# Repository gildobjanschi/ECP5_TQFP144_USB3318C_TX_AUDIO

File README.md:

# ECP5 High Speed USB Audio Board
This project aims to implement a High Speed USB audio interface using the Lattice Semiconductor ECP5 FPGA coupled with a USB3318C ULPI USB interface.

## Software
The FPGA Verilog software for the board is currently being developed in a private Github project. Once the board and the code are verified this page will be updated with a link to that project.

## Project Status
The board was manufactured and it is fully functional.

[Schematic PDF](https://github.com/gildobjanschi/ECP5_TQFP144_USB3318C_TX_AUDIO/blob/main/kicad/ECP5%20Audio%20Tx.pdf)

## How to setup KiCAD
Checkout the project and open it. In the Configure Paths dialog add: Name: ECP5_AUDIO and Path: "full path to your GitHub directory"/GitHub/ECP5_TQFP144_USB3318C_TX_AUDIO

In the Manage Symbol Libraries click the Project Specific Libraries and add: Name: ECP5_AUDIO and Library Path: ${ECP5_AUDIO}/symbols/Symbols.kicad_sym

In the Manage Footprint Libraries click the Project Specific Libraries and add: Name: ECP5_AUDIO and Library Path: ${ECP5_AUDIO}/footprints/Footprints.pretty

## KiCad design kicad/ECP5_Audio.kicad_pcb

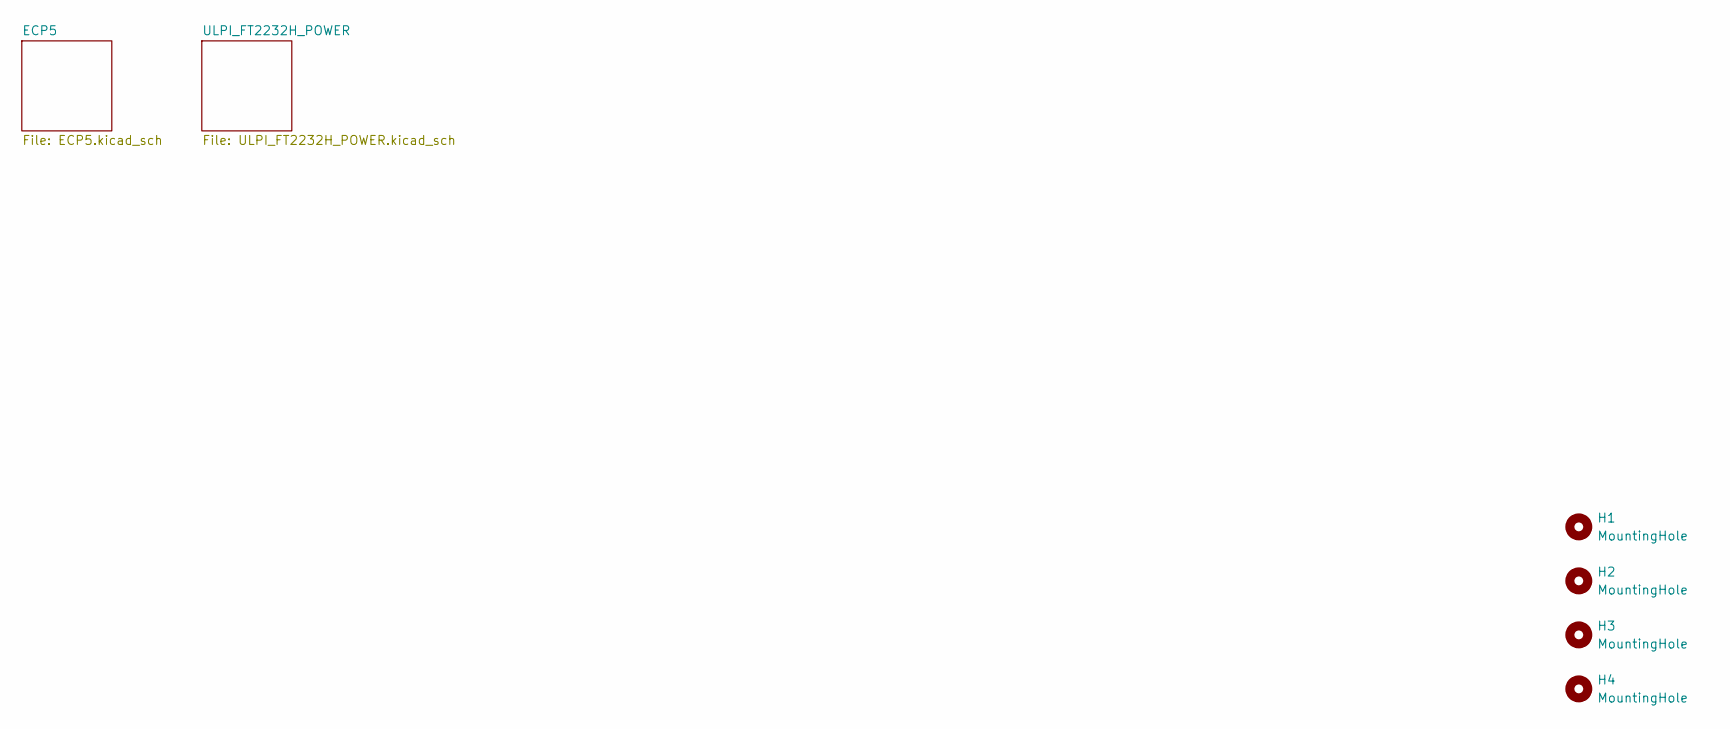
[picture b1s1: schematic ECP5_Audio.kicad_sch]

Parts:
H1, H2, H3, H4: MountingHole; MountingHole_3.2mm_M3

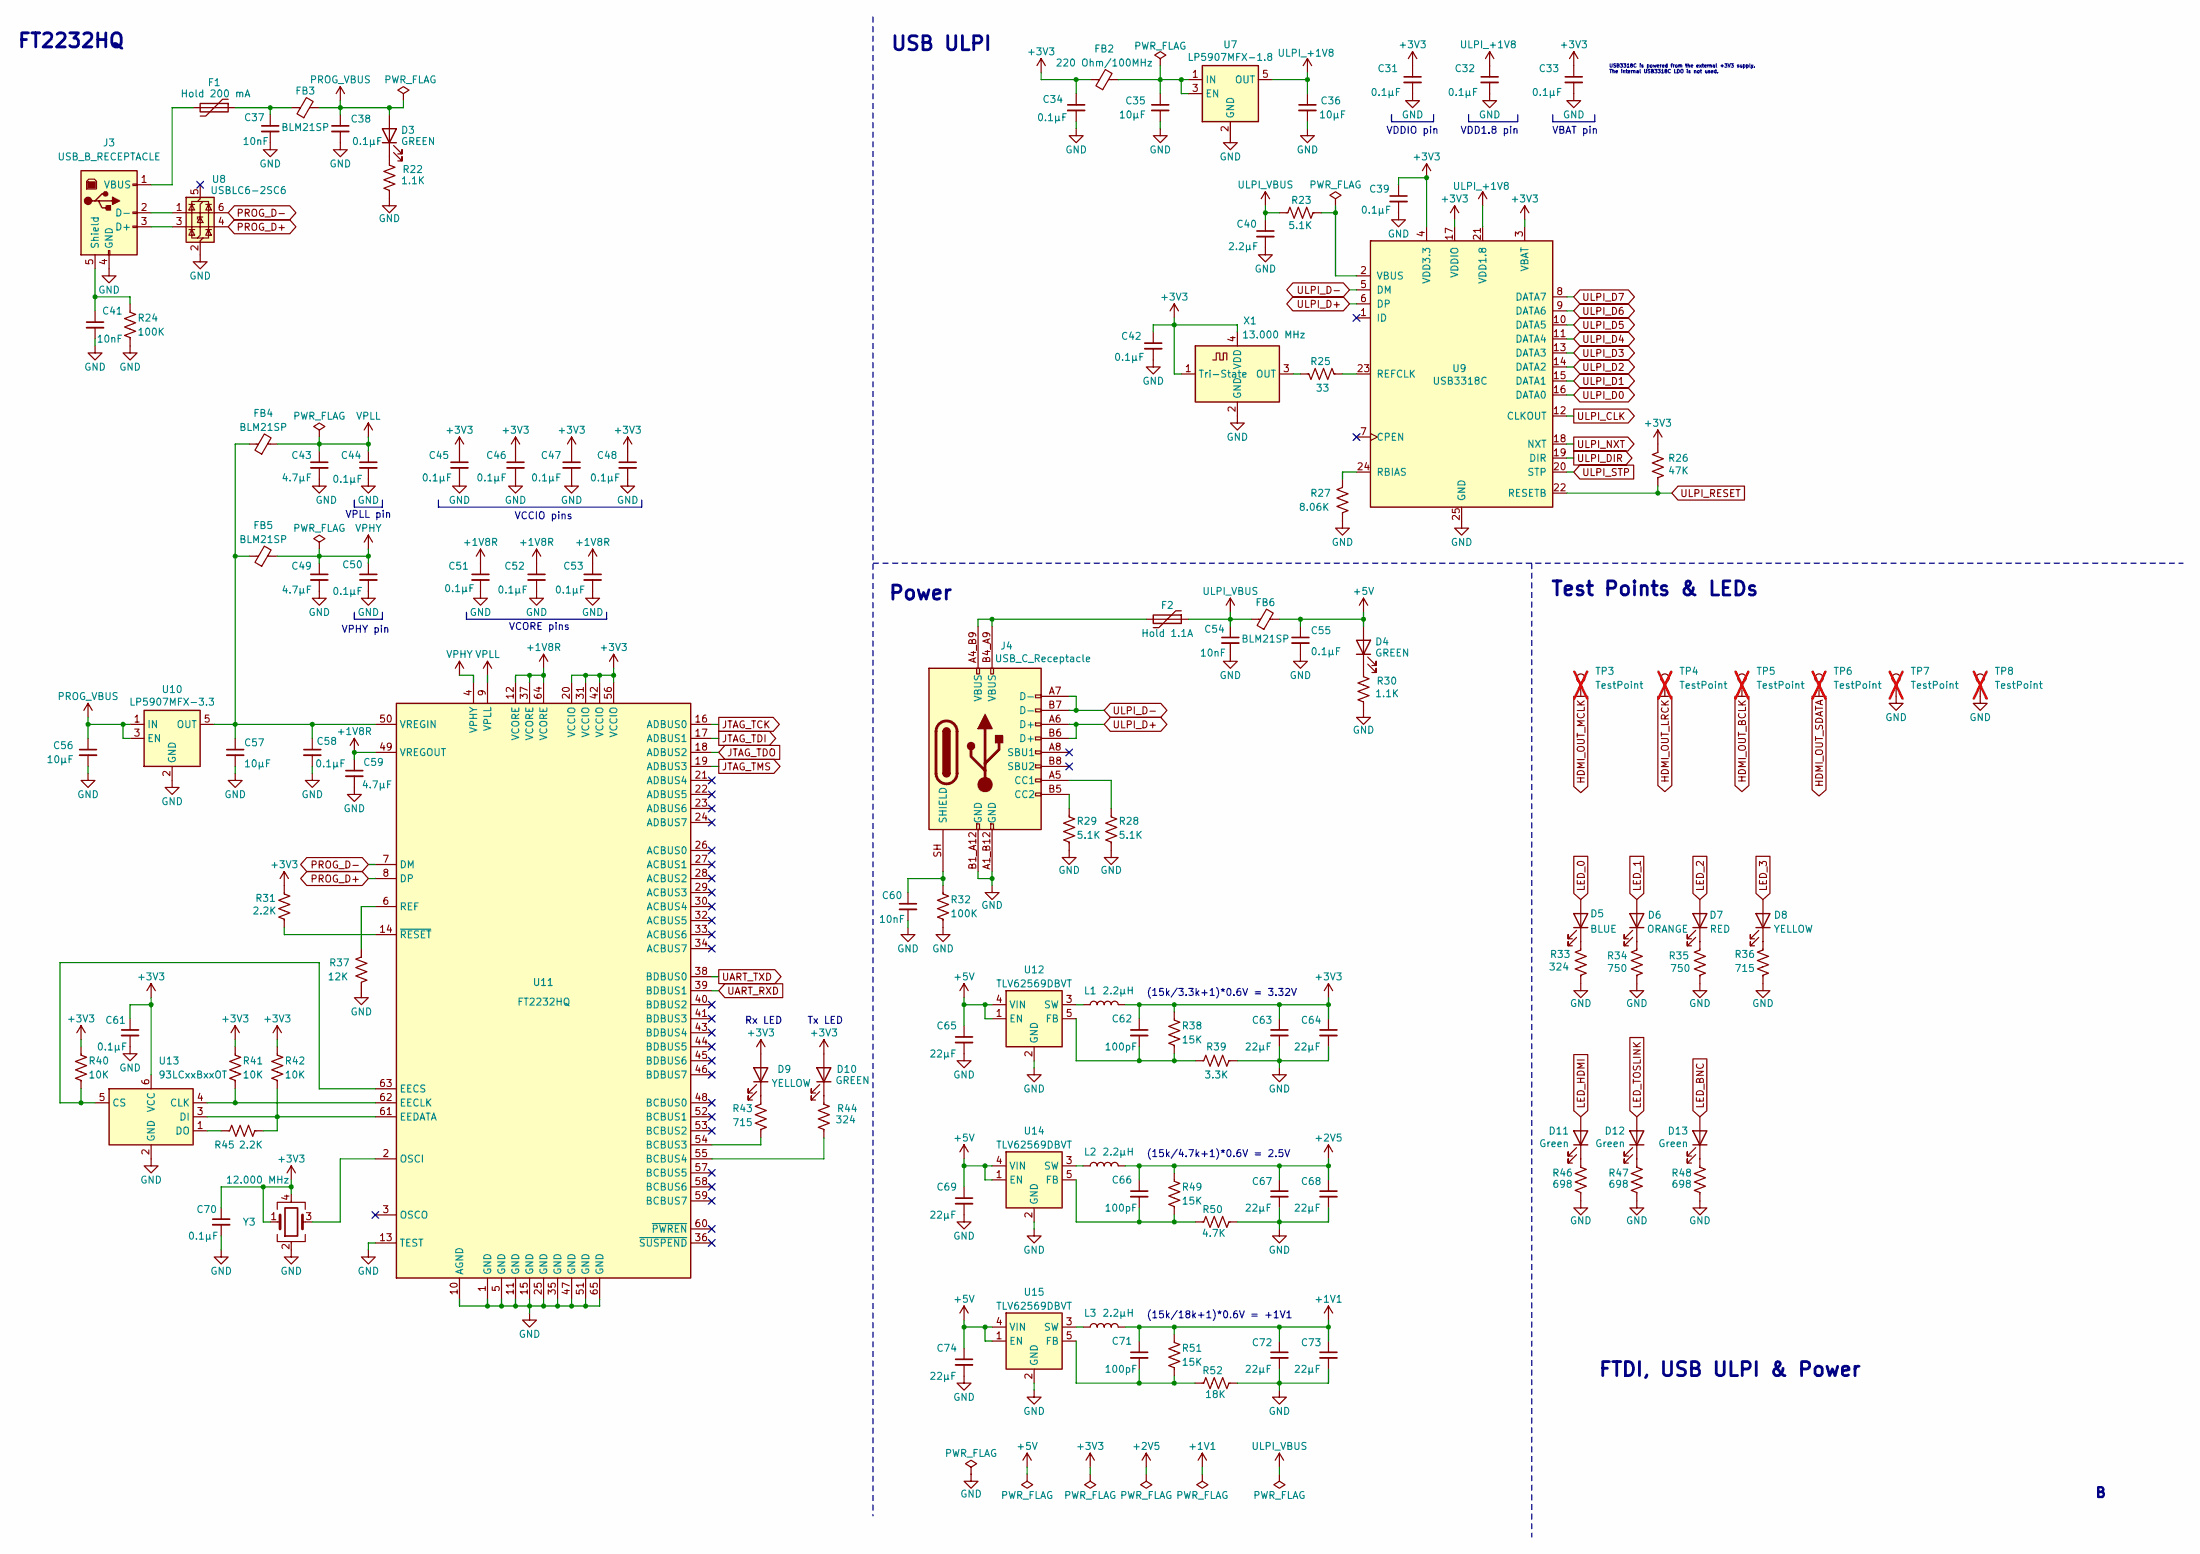
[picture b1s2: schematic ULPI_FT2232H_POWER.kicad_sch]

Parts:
C31, C32, C33, C34, C38, C39, C42, C44, C45, C46, C47, C48, C50, C51, C52, C53, C55, C58, C61, C70: 0.1µF; C_0603_1608Metric; MPN CL10B104KB8NNNC
C35, C36, C56, C57: 10µF; C_0805_2012Metric; MPN CL21B106KOQNNNE
C37, C41, C54, C60: 10nF; C_0603_1608Metric; MPN CL10B103KB8NNNC
C40: 2.2µF; C_0603_1608Metric; MPN CL10B225KP8NNNC
C43, C49, C59: 4.7µF; C_0603_1608Metric; MPN CL10A475KL8NRNC
C62, C66, C71: 100pF; C_0603_1608Metric; MPN CL10C101FB81PNC
C63, C64, C65, C67, C68, C69, C72, C73, C74: 22µF; C_0805_2012Metric; MPN CL21A226KOQNNNE
D3, D4, D10: GREEN; LED_0603_1608Metric; MPN APT1608LZGCK
D5: BLUE; LED_0603_1608Metric; MPN APT1608LVBC/D
D6: ORANGE; LED_0603_1608Metric; MPN APT1608LSECK/J4-PRV
D7: RED; LED_0603_1608Metric; MPN APT1608LSECK/J3-PRV
D8, D9: YELLOW; LED_0603_1608Metric; MPN APT1608LSYCK
D11, D12, D13: Green; Dialight_551-0307F; MPN 5511307F
F1: Hold 200 mA; Bel_Fuse_1812; MPN 0ZCG0020AF2C
F2: Hold 1.1A; Bel_Fuse_1812; MPN 0ZCG0110AF2C
FB2: 220 Ohm/100MHz; L_0603_1608Metric; MPN MPZ1608S221ATA00
FB3, FB4, FB5, FB6: BLM21SP; L_0805_2012Metric; MPN BLM21SP601SN1D
J3: USB_B_RECEPTACLE; CUI_UJ2-BH-BL1-TH; MPN UJ2-BH-BL1-TH
J4: USB_C_Receptacle; GCT_USB4105GFA120; MPN USB4105-GF-A-120
L1, L2, L3: 2.2µH; L_1210_3225Metric; MPN DFE322512F-2R2M=P2
R22, R30: 1.1K; R_0603_1608Metric; MPN ERJ-3EKF1101V
R23, R28, R29: 5.1K; R_0603_1608Metric; MPN ERJ-3EKF5101V
R24, R32: 100K; R_0603_1608Metric; MPN ERJ-3EKF1003V
R25: 33; R_0603_1608Metric; MPN ERJ-3EKF33R0V
R26: 47K; R_0603_1608Metric; MPN ERJ-3EKF4702V
R27: 8.06K; R_0603_1608Metric; MPN ERJ-3EKF8061V
R31, R45: 2.2K; R_0603_1608Metric; MPN ERJ-3EKF2201V
R33, R44: 324; R_0603_1608Metric; MPN ERJ-3EKF3240V
R34, R35: 750; R_0603_1608Metric; MPN ERJ-3EKF7500V
R36, R43: 715; R_0603_1608Metric; MPN ERJ-3EKF7150V
R37: 12K; R_0603_1608Metric; MPN ERJ-3EKF1202V
R38, R49, R51: 15K; R_0603_1608Metric; MPN ERJ-3EKF1502V
R39: 3.3K; R_0603_1608Metric; MPN ERJ-3EKF3301V
R40, R41, R42: 10K; R_0603_1608Metric; MPN ERJ-3EKF1002V
R46, R47, R48: 698; R_0603_1608Metric; MPN ERJ-3EKF6980V
R50: 4.7K; R_0603_1608Metric; MPN ERJ-3EKF4701V
R52: 18K; R_0603_1608Metric; MPN ERJ-3EKF1802V
TP3, TP4, TP5, TP6: TestPoint; TestPoint_Keystone_5000-5004_Miniature; MPN 5004; not fitted
TP7, TP8: TestPoint; TestPoint_Keystone_5000-5004_Miniature; MPN 5001; not fitted
U7: LP5907MFX-1.8; SOT-23-5; MPN LP5907MFX-1.8/NOPB
U8: USBLC6-2SC6; SOT-23-6; MPN USBLC6-2SC6
U9: USB3318C; QFN-24-1EP_4x4mm_P0.5mm_EP2.65x2.65mm_ThermalVias; MPN USB3318C-CP-TR
U10: LP5907MFX-3.3; SOT-23-5; MPN LP5907MFX-3.3/NOPB
U11: FT2232HQ; QFN-64-1EP_9x9mm_P0.5mm_EP4.35x4.35mm; MPN FT2232HQ-REEL
U12, U14, U15: TLV62569DBVT; SOT-23-5; MPN TLV62569DBVT
U13: 93LCxxBxxOT; SOT-23-6; MPN 93LC56BT-I/OT
X1: 13.000 MHz; Oscillator_SMD_ECS_2520MV-xxx-xx-4Pin_2.5x2.0mm; MPN ECS-2520MV-130-BN-TR
Y3: 12.000 MHz; Oscillator_SMD_ECS_2520MV-xxx-xx-4Pin_2.5x2.0mm; MPN SG-210STF 12.0000ML3

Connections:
+1V1: C71.1, C72.1, C73.1, L3.2, R51.1; also elsewhere on the board
+1V8R: C51.1, C52.1, C53.1, C59.1, U11.12 (VCORE), U11.37 (VCORE), U11.49 (VREGOUT), U11.64 (VCORE)
+2V5: C66.1, C67.1, C68.1, L2.2, R49.1; also elsewhere on the board
+3V3: C31.1, C33.1, C34.1, C39.1, C42.1, C45.1, C46.1, C47.1, C48.1, C61.1, C62.1, C63.1, C64.1, C70.1, D9.2 (A), D10.2 (A), FB2.1, L1.2, R26.2, R31.1, R38.1, R40.1, R41.1, R42.1, U9.3 (VBAT), U9.4 (VDD3.3), U9.17 (VDDIO), U11.20 (VCCIO), U11.31 (VCCIO), U11.42 (VCCIO), U11.56 (VCCIO), U13.6 (VCC), X1.1 (Tri-State), X1.4 (VDD), Y3.1, Y3.4; also elsewhere on the board
+5V: C55.1, C65.1, C69.1, C74.1, D4.2 (A), FB6.2, U12.1 (EN), U12.4 (VIN), U14.1 (EN), U14.4 (VIN), U15.1 (EN), U15.4 (VIN); also elsewhere on the board
GND: C31.2, C32.2, C33.2, C34.2, C35.2, C36.2, C37.2, C38.2, C39.2, C40.2, C41.2, C42.2, C43.2, C44.2, C45.2, C46.2, C47.2, C48.2, C49.2, C50.2, C51.2, C52.2, C53.2, C54.2, C55.2, C56.2, C57.2, C58.2, C59.2, C60.2, C61.2, C63.2, C64.2, C65.2, C67.2, C68.2, C69.2, C70.2, C72.2, C73.2, C74.2, J3.4 (GND), J4.A1_B12 (GND), J4.B1_A12 (GND), R22.2, R24.2, R27.2, R28.2, R29.2, R30.2, R32.2, R33.2, R34.2, R35.2, R36.2, R37.2, R39.2, R46.2, R47.2, R48.2, R50.2, R52.2, TP7.1, TP8.1, U7.2 (GND), U8.2 (GND), U9.25 (GND), U10.2 (GND), U11.1 (GND), U11.5 (GND), U11.10 (AGND), U11.11 (GND), U11.13 (TEST), U11.15 (GND), U11.25 (GND), U11.35 (GND), U11.47 (GND), U11.51 (GND), U11.65 (GND), U12.2 (GND), U13.2 (GND), U14.2 (GND), U15.2 (GND), X1.2 (GND), Y3.2; also elsewhere on the board
HDMI_OUT_BCLK: TP5.1; also elsewhere on the board
HDMI_OUT_LRCK: TP4.1; also elsewhere on the board
HDMI_OUT_MCLK: TP3.1; also elsewhere on the board
HDMI_OUT_SDATA: TP6.1; also elsewhere on the board
JTAG_TCK: U11.16 (ADBUS0); also elsewhere on the board
JTAG_TDI: U11.17 (ADBUS1); also elsewhere on the board
JTAG_TDO: U11.18 (ADBUS2); also elsewhere on the board
JTAG_TMS: U11.19 (ADBUS3); also elsewhere on the board
LED_0: D5.2 (A); also elsewhere on the board
LED_1: D6.2 (A); also elsewhere on the board
LED_2: D7.2 (A); also elsewhere on the board
LED_3: D8.2 (A); also elsewhere on the board
LED_BNC: D13.2 (A); also elsewhere on the board
LED_HDMI: D11.2 (A); also elsewhere on the board
LED_TOSLINK: D12.2 (A); also elsewhere on the board
unnamed: C37.1, F1.1, FB3.1
unnamed: D3.1 (K), R22.1
unnamed: D4.1 (K), R30.1
unnamed: D5.1 (K), R33.1
unnamed: D6.1 (K), R34.1
unnamed: D7.1 (K), R35.1
unnamed: D8.1 (K), R36.1
unnamed: D9.1 (K), R43.1
unnamed: D10.1 (K), R44.1
unnamed: D11.1 (K), R46.1
unnamed: D12.1 (K), R47.1
unnamed: D13.1 (K), R48.1
unnamed: F2.2, J4.A4_B9 (VBUS), J4.B4_A9 (VBUS)
unnamed: J3.3 (D+), U8.3 (I/O2)
unnamed: J3.2 (D-), U8.1 (I/O1)
unnamed: C41.1, J3.5 (Shield), R24.1
unnamed: F1.2, J3.1 (VBUS)
unnamed: J4.A5 (CC1), R28.1
unnamed: J4.B5 (CC2), R29.1
unnamed: C60.1, J4.SH (SHIELD), R32.1
unnamed: C35.1, FB2.2, U7.1 (IN), U7.3 (EN)
unnamed: R27.1, U9.24 (RBIAS)
unnamed: R25.2, U9.23 (REFCLK)
unnamed: R23.1, U9.2 (VBUS)
unnamed: C57.1, C58.1, FB4.1, FB5.1, U10.5 (OUT), U11.50 (VREGIN)
unnamed: R43.2, U11.54 (BCBUS3)
unnamed: R44.2, U11.55 (BCBUS4)
unnamed: R41.2, U11.62 (EECLK), U13.4 (CLK)
unnamed: R40.2, U11.63 (EECS), U13.5 (CS)
unnamed: R42.2, R45.2, U11.61 (EEDATA), U13.3 (DI)
unnamed: U11.2 (OSCI), Y3.3
unnamed: R37.1, U11.6 (REF)
unnamed: R31.2, U11.14 (~RESET)
unnamed: C62.2, R38.2, R39.1, U12.5 (FB)
unnamed: L1.1, U12.3 (SW)
unnamed: R45.1, U13.1 (DO)
unnamed: C66.2, R49.2, R50.1, U14.5 (FB)
unnamed: L2.1, U14.3 (SW)
unnamed: C71.2, R51.2, R52.1, U15.5 (FB)
unnamed: L3.1, U15.3 (SW)
unnamed: R25.1, X1.3 (OUT)
PROG_D+: U8.4 (I/O2), U11.8 (DP)
PROG_D-: U8.6 (I/O1), U11.7 (DM)
PROG_VBUS: C38.1, C56.1, D3.2 (A), FB3.2, U10.1 (IN), U10.3 (EN)
UART_RXD: U11.39 (BDBUS1); also elsewhere on the board
UART_TXD: U11.38 (BDBUS0); also elsewhere on the board
ULPI_+1V8: C32.1, C36.1, U7.5 (OUT), U9.21 (VDD1.8)
ULPI_CLK: U9.12 (CLKOUT); also elsewhere on the board
ULPI_D0: U9.16 (DATA0); also elsewhere on the board
ULPI_D1: U9.15 (DATA1); also elsewhere on the board
ULPI_D2: U9.14 (DATA2); also elsewhere on the board
ULPI_D3: U9.13 (DATA3); also elsewhere on the board
ULPI_D4: U9.11 (DATA4); also elsewhere on the board
ULPI_D5: U9.10 (DATA5); also elsewhere on the board
ULPI_D6: U9.9 (DATA6); also elsewhere on the board
ULPI_D7: U9.8 (DATA7); also elsewhere on the board
ULPI_D+: J4.A6 (D+), J4.B6 (D+), U9.6 (DP)
ULPI_D-: J4.A7 (D-), J4.B7 (D-), U9.5 (DM)
ULPI_DIR: U9.19 (DIR); also elsewhere on the board
ULPI_NXT: U9.18 (NXT); also elsewhere on the board
ULPI_RESET: R26.1, U9.22 (RESETB); also elsewhere on the board
ULPI_STP: U9.20 (STP); also elsewhere on the board
ULPI_VBUS: C40.1, C54.1, F2.1, FB6.1, R23.2
VPHY: C49.1, C50.1, FB5.2, U11.4 (VPHY)
VPLL: C43.1, C44.1, FB4.2, U11.9 (VPLL)

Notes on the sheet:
VPLL pin
VCCIO pins
(15k/4.7k+1)*0.6V = 2.5V
Test Points & LEDs
Power
VCORE pins
VPHY pin
(15k/18k+1)*0.6V = +1V1
VDD1.8 pin
USB ULPI
Rx LED
FTDI, USB ULPI & Power
USB3318C is powered from the external +3V3 supply. The internal USB3318C LDO is not used.
Tx LED
VDDIO pin
VBAT pin
FT2232HQ
(15k/3.3k+1)*0.6V = 3.32V

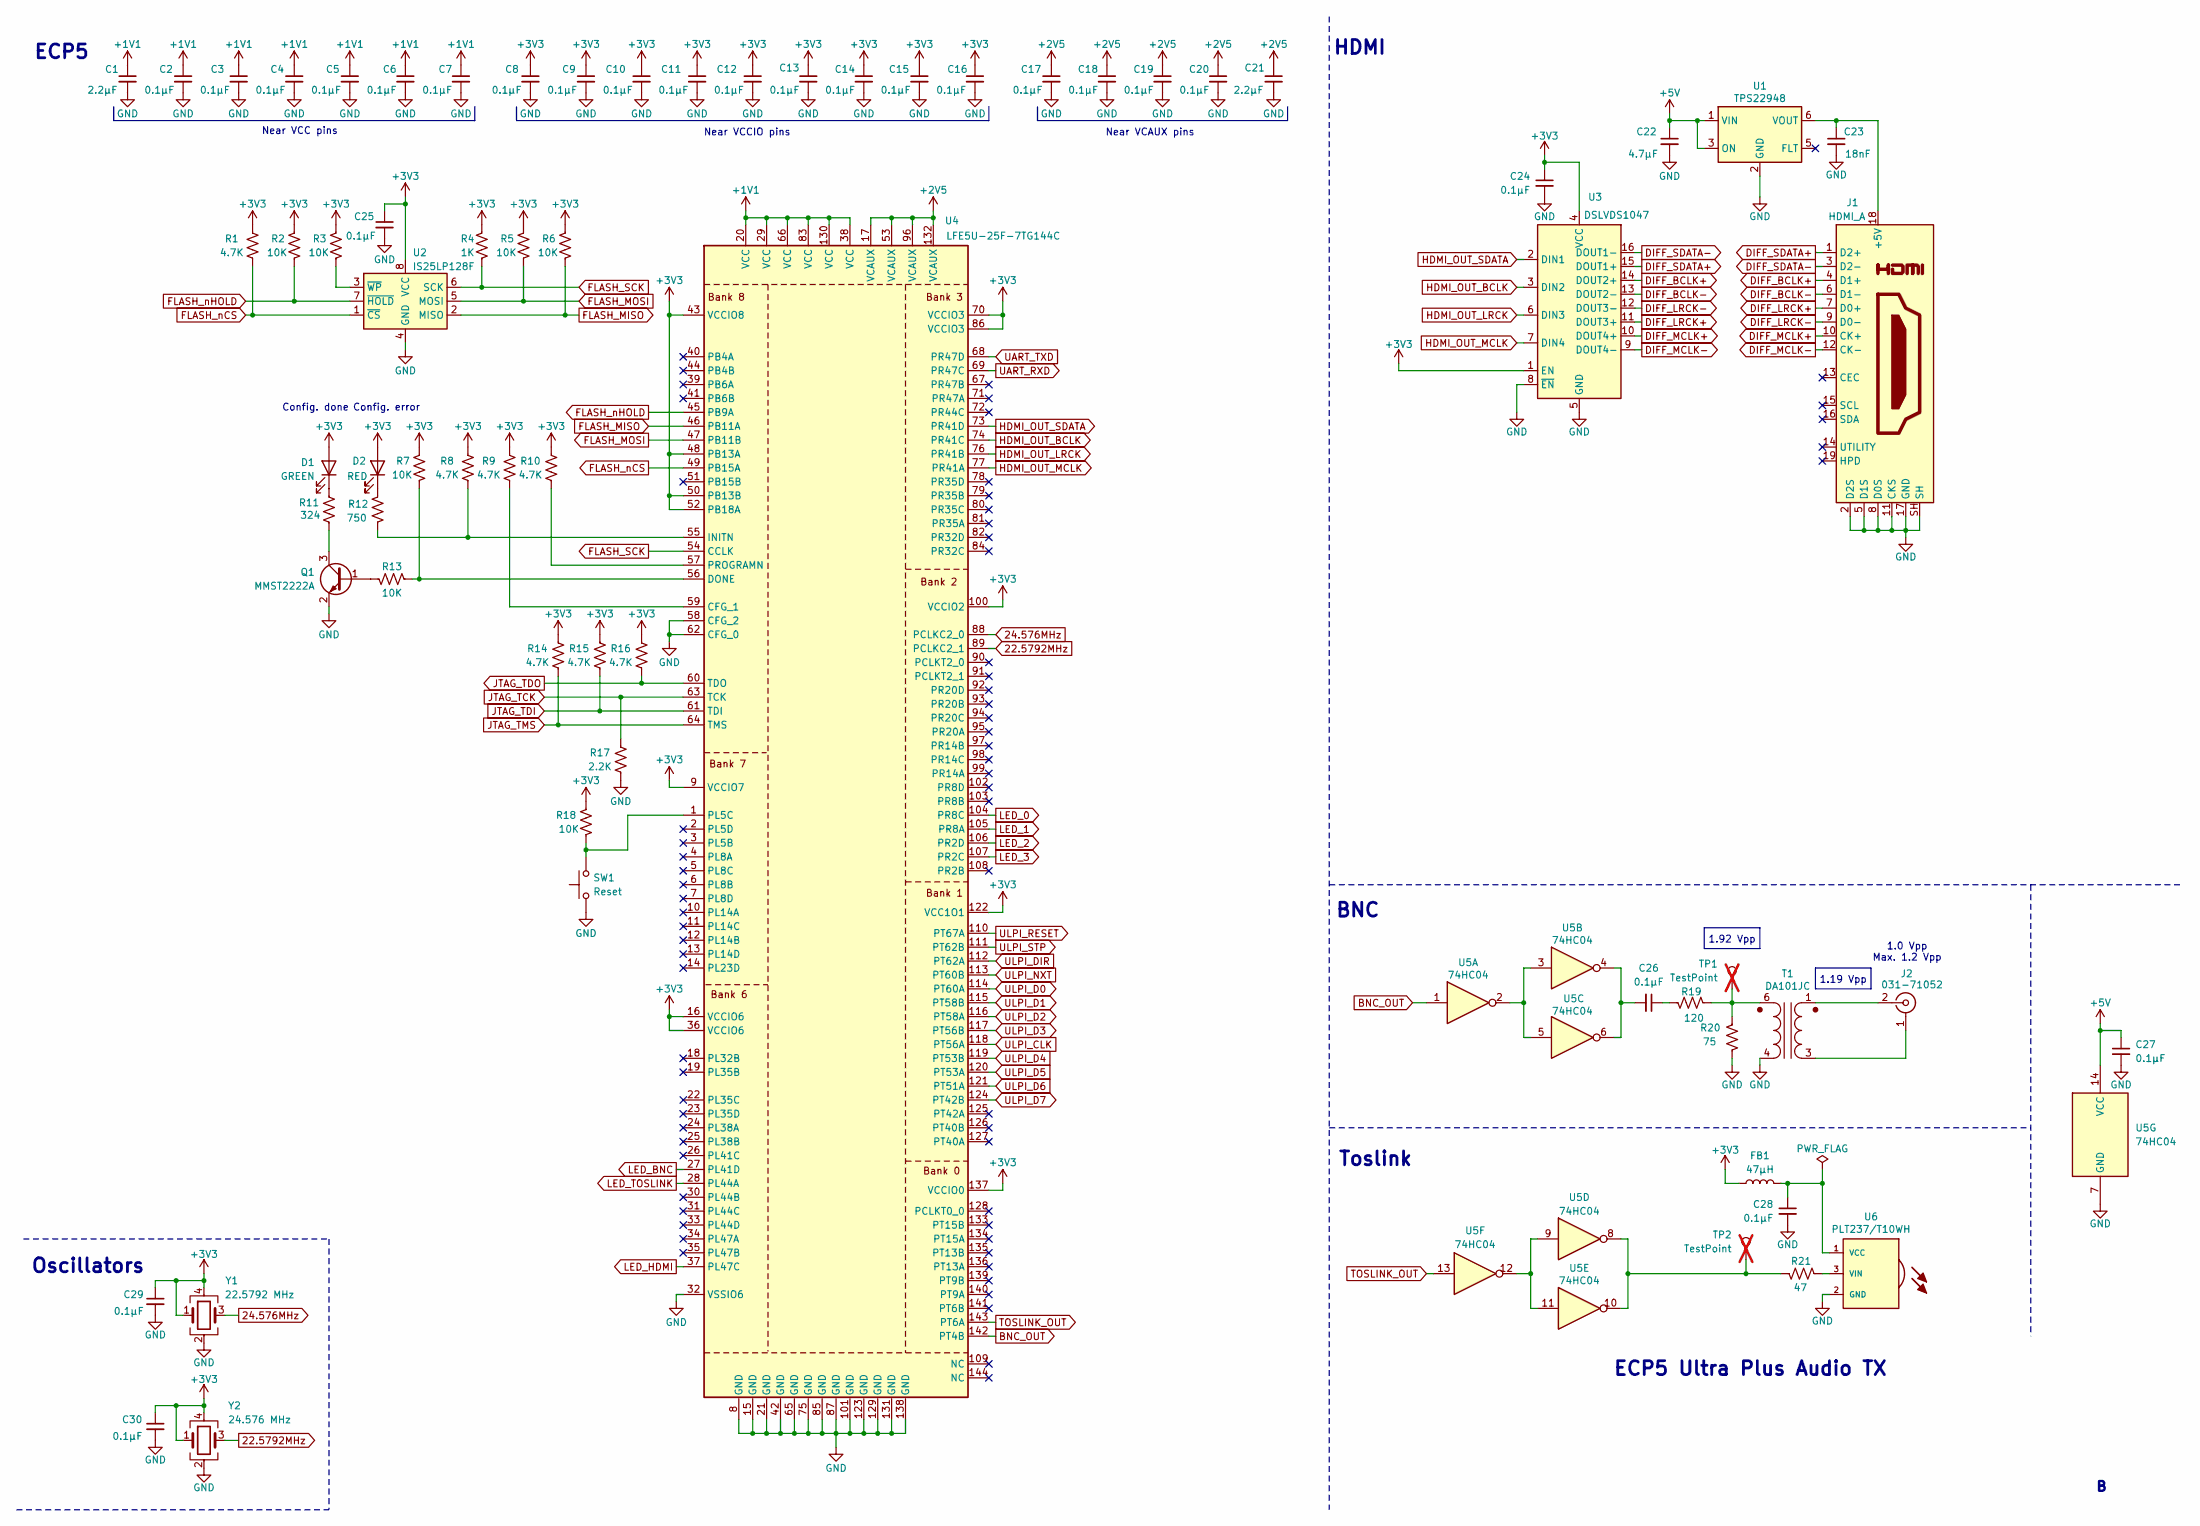
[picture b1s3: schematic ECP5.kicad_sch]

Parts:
C1, C21: 2.2µF; C_0603_1608Metric; MPN CL10B225KP8NNNC
C2, C3, C4, C5, C6, C7, C8, C9, C10, C11, C12, C13, C14, C15, C16, C17, C18, C19, C20, C24, C25, C26, C27, C28, C29, C30: 0.1µF; C_0603_1608Metric; MPN CL10B104KB8NNNC
C22: 4.7µF; C_0603_1608Metric; MPN CL10A475KL8NRNC
C23: 18nF; C_0603_1608Metric; MPN CC0603KRX7R9BB183
D1: GREEN; LED_0603_1608Metric; MPN APT1608LZGCK
D2: RED; LED_0603_1608Metric; MPN APT1608LSECK/J3-PRV
FB1: 47µH; L_0805_2012Metric; MPN LQM21DN470M70L
J1: HDMI_A; AMPHENOL_10029449-001RLF; MPN 10029449-001RLF
J2: 031-71052; BNC_Amphenol_031-71052_Horizontal; MPN 031-71052
Q1: MMST2222A; SOT-323_SC-70; MPN MMST2222A-7-F
R1, R8, R9, R10, R14, R15, R16: 4.7K; R_0603_1608Metric; MPN ERJ-3EKF4701V
R2, R3, R5, R6, R7, R13, R18: 10K; R_0603_1608Metric; MPN ERJ-3EKF1002V
R4: 1K; R_0603_1608Metric; MPN ERJ-3EKF1001V
R11: 324; R_0603_1608Metric; MPN ERJ-3EKF3240V
R12: 750; R_0603_1608Metric; MPN ERJ-3EKF7500V
R17: 2.2K; R_0603_1608Metric; MPN ERJ-3EKF2201V
R19: 120; R_0603_1608Metric; MPN ERJ-3EKF1200V
R20: 75; R_0603_1608Metric; MPN ERJ-3EKF75R0V
R21: 47; R_0603_1608Metric; MPN ERJ-3EKF47R0V
SW1: Reset; SW_SPST_PTS645; MPN PTS645SK43SMTR92 LFS
T1: DA101JC; DA101J_MUR; MPN DA101JC
TP1, TP2: TestPoint; TestPoint_Keystone_5000-5004_Miniature; MPN 5004; not fitted
U1: TPS22948; SOT-363_SC-70-6; MPN TPS22948DCKR
U2: IS25LP128F; WDFN-8-1EP_6x5mm_P1.27mm_EP3.4x4mm; MPN IS25LP128-JKLE
U3: DSLVDS1047; TSSOP-16-1EP_4.4x5mm_P0.65mm; MPN DSLVDS1047PWR
U4: LFE5U-25F-7TG144C; TQFP-144_20x20mm_P0.5mm; MPN LFE5U-25F-7TG144C
U5: 74HC04; TSSOP-14_4.4x5mm_P0.65mm; MPN SN74HC04PWR
U6: PLT237/T10WH; PLR135-T10; MPN PLT237/T10WH
Y1: 22.5792 MHz; CCHD-957; MPN CCHD-957-25-22.5792
Y2: 24.576 MHz; CCHD-957; MPN CCHD-957-25-24.576

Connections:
22.5792MHz: U4.89 (PCLKC2_1), Y2.3 (OUT)
24.576MHz: U4.88 (PCLKC2_0), Y1.3 (OUT)
+1V1: C1.1, C2.1, C3.1, C4.1, C5.1, C6.1, C7.1, U4.20 (VCC), U4.29 (VCC), U4.38 (VCC), U4.66 (VCC), U4.83 (VCC), U4.130 (VCC); also elsewhere on the board
+2V5: C17.1, C18.1, C19.1, C20.1, C21.1, U4.17 (VCAUX), U4.53 (VCAUX), U4.96 (VCAUX), U4.132 (VCAUX); also elsewhere on the board
+3V3: C8.1, C9.1, C10.1, C11.1, C12.1, C13.1, C14.1, C15.1, C16.1, C24.1, C25.1, C29.1, C30.1, D1.2 (A), D2.2 (A), FB1.2, R1.2, R2.2, R3.2, R4.1, R5.2, R6.2, R7.2, R8.2, R9.2, R10.2, R14.2, R15.2, R16.2, R18.2, U2.8 (VCC), U3.1 (EN), U3.4 (VCC), U4.9 (VCCIO7), U4.16 (VCCIO6), U4.36 (VCCIO6), U4.43 (VCCIO8), U4.48 (PB13A), U4.50 (PB13B), U4.52 (PB18A), U4.70 (VCCIO3), U4.86 (VCCIO3), U4.100 (VCCIO2), U4.122 (VCC1O1), U4.137 (VCCIO0), Y1.1 (E/D), Y1.4 (VCC), Y2.1 (E/D), Y2.4 (VCC); also elsewhere on the board
+5V: C22.1, C27.1, U1.1 (VIN), U1.3 (ON), U5.14 (VCC); also elsewhere on the board
BNC_OUT: U4.142 (PT4B), U5.1
DIFF_BCLK+: J1.4 (D1+), U3.14 (DOUT2+)
DIFF_BCLK-: J1.6 (D1-), U3.13 (DOUT2-)
DIFF_LRCK+: J1.7 (D0+), U3.11 (DOUT3+)
DIFF_LRCK-: J1.9 (D0-), U3.12 (DOUT3-)
DIFF_MCLK+: J1.10 (CK+), U3.10 (DOUT4+)
DIFF_MCLK-: J1.12 (CK-), U3.9 (DOUT4-)
DIFF_SDATA+: J1.1 (D2+), U3.15 (DOUT1+)
DIFF_SDATA-: J1.3 (D2-), U3.16 (DOUT1-)
FLASH_MISO: R6.1, U2.2 (MISO), U4.46 (PB11A)
FLASH_MOSI: R5.1, U2.5 (MOSI), U4.47 (PB11B)
FLASH_SCK: R4.2, U2.6 (SCK), U4.54 (CCLK)
FLASH_nCS: R1.1, U2.1 (~CS), U4.49 (PB15A)
FLASH_nHOLD: R2.1, U2.7 (~HOLD), U4.45 (PB9A)
GND: C1.2, C2.2, C3.2, C4.2, C5.2, C6.2, C7.2, C8.2, C9.2, C10.2, C11.2, C12.2, C13.2, C14.2, C15.2, C16.2, C17.2, C18.2, C19.2, C20.2, C21.2, C22.2, C23.2, C24.2, C25.2, C27.2, C28.2, C29.2, C30.2, J1.2 (D2S), J1.5 (D1S), J1.8 (D0S), J1.11 (CKS), J1.17 (GND), J1.SH, Q1.2 (E), R17.1, R20.2, SW1.1, T1.4 (SA), U1.2 (GND), U2.4 (GND), U2.9 (GND), U3.5 (GND), U3.8 (~EN), U4.8 (GND), U4.15 (GND), U4.21 (GND), U4.32 (VSSIO6), U4.42 (GND), U4.58 (CFG_2), U4.62 (CFG_0), U4.65 (GND), U4.75 (GND), U4.85 (GND), U4.87 (GND), U4.101 (GND), U4.123 (GND), U4.129 (GND), U4.131 (GND), U4.138 (GND), U5.7 (GND), U6.2 (GND), Y1.2 (GND), Y2.2 (GND); also elsewhere on the board
HDMI_OUT_BCLK: U3.3 (DIN2), U4.74 (PR41C); also elsewhere on the board
HDMI_OUT_LRCK: U3.6 (DIN3), U4.76 (PR41B); also elsewhere on the board
HDMI_OUT_MCLK: U3.7 (DIN4), U4.77 (PR41A); also elsewhere on the board
HDMI_OUT_SDATA: U3.2 (DIN1), U4.73 (PR41D); also elsewhere on the board
JTAG_TCK: R17.2, U4.63 (TCK); also elsewhere on the board
JTAG_TDI: R15.1, U4.61 (TDI); also elsewhere on the board
JTAG_TDO: R16.1, U4.60 (TDO); also elsewhere on the board
JTAG_TMS: R14.1, U4.64 (TMS); also elsewhere on the board
LED_0: U4.104 (PR8C); also elsewhere on the board
LED_1: U4.105 (PR8A); also elsewhere on the board
LED_2: U4.106 (PR2D); also elsewhere on the board
LED_3: U4.107 (PR2C); also elsewhere on the board
LED_BNC: U4.27 (PL41D); also elsewhere on the board
LED_HDMI: U4.37 (PL47C); also elsewhere on the board
LED_TOSLINK: U4.28 (PL44A); also elsewhere on the board
unnamed: C26.1, R19.2
unnamed: C26.2, U5.4, U5.6
unnamed: D1.1 (K), R11.1
unnamed: D2.1 (K), R12.1
unnamed: C23.1, J1.18 (+5V), U1.6 (VOUT)
unnamed: J2.1 (Ext), T1.3 (AB)
unnamed: J2.2 (In), T1.1 (AA)
unnamed: Q1.1 (B), R13.1
unnamed: Q1.3 (C), R11.2
unnamed: R21.2, TP2.1, U5.8, U5.10
unnamed: R19.1, R20.1, T1.6 (SB), TP1.1
unnamed: R3.1, U2.3 (~WP)
unnamed: R9.1, U4.59 (CFG_1)
unnamed: R7.1, R13.2, U4.56 (DONE)
unnamed: R8.1, R12.2, U4.55 (INITN)
unnamed: R18.1, SW1.2, U4.1 (PL5C)
unnamed: R10.1, U4.57 (PROGRAMN)
unnamed: U5.2, U5.3, U5.5
unnamed: U5.9, U5.11, U5.12
unnamed: C28.1, FB1.1, U6.1 (VCC)
unnamed: R21.1, U6.3 (VIN)
TOSLINK_OUT: U4.143 (PT6A), U5.13
UART_RXD: U4.69 (PR47C); also elsewhere on the board
UART_TXD: U4.68 (PR47D); also elsewhere on the board
ULPI_CLK: U4.118 (PT56A); also elsewhere on the board
ULPI_D0: U4.114 (PT60A); also elsewhere on the board
ULPI_D1: U4.115 (PT58B); also elsewhere on the board
ULPI_D2: U4.116 (PT58A); also elsewhere on the board
ULPI_D3: U4.117 (PT56B); also elsewhere on the board
ULPI_D4: U4.119 (PT53B); also elsewhere on the board
ULPI_D5: U4.120 (PT53A); also elsewhere on the board
ULPI_D6: U4.121 (PT51A); also elsewhere on the board
ULPI_D7: U4.124 (PT42B); also elsewhere on the board
ULPI_DIR: U4.112 (PT62A); also elsewhere on the board
ULPI_NXT: U4.113 (PT60B); also elsewhere on the board
ULPI_RESET: U4.110 (PT67A); also elsewhere on the board
ULPI_STP: U4.111 (PT62B); also elsewhere on the board

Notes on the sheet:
ECP5
1.92 Vpp
Toslink
Config. error
1.19 Vpp
HDMI
BNC
ECP5 Ultra Plus Audio TX
Near VCCIO pins
1.0 Vpp Max. 1.2 Vpp
Config. done
Near VCAUX pins
Oscillators
Near VCC pins

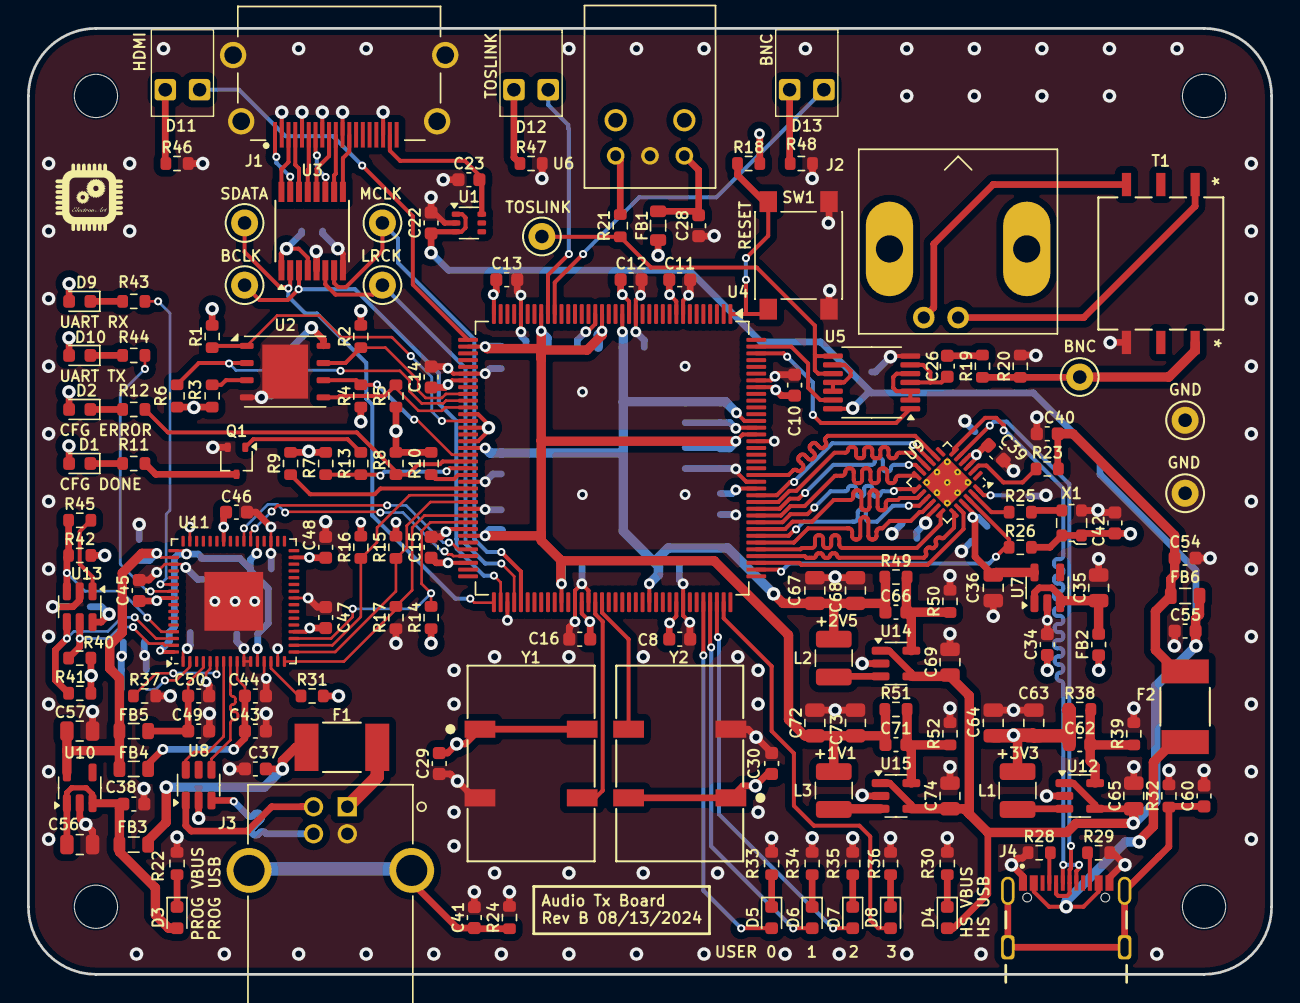
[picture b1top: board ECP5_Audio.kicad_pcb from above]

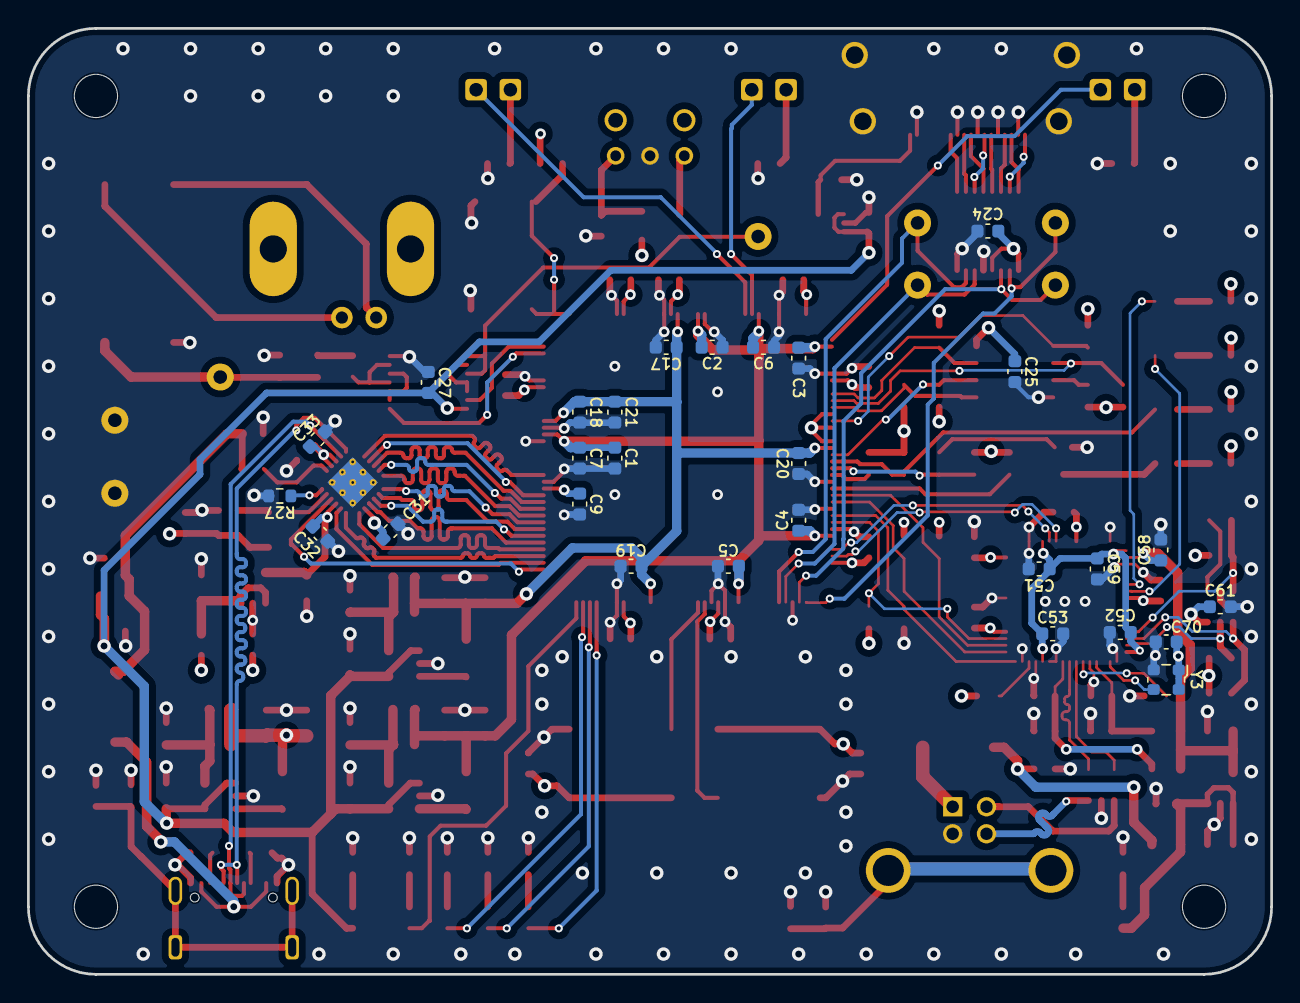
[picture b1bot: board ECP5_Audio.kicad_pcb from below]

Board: 4 copper layers, 92.0 x 70.0 mm, 188 parts (28 on the bottom side), 124 nets.

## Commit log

2024-07-15 Moved 8.06K resistor close to USB3318C
    Moved 8.06K resistor close to USB3318C
2024-07-16 Prepared submission to PCBWay
2024-07-16 Upgraded to ECP5-25K
2024-08-08 Added PDF file.
2024-08-08 Added 3d view
2024-08-13 5.1K USB resistors
    Replaces 22K resistors to VBUS with 5.1K resistors to GND.
2024-08-13 Updated ROM symbol
2024-08-14 Delete STM32H723.kicad_sch
    Remove unused file.
2024-08-15 Update path to 3D models
